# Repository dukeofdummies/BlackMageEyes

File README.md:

# BlackMageEyes
For the code behind the eyes here https://www.youtube.com/watch?v=K9V43iSXRQA

The main gyst of this code is to read button pushes (contact closures) from a controller to change patterns in Adafruit's Neopixel Array.

For details on the Hardware behind it see here
https://www.deviantart.com/dukeofdummies

This current eye pattern is one strand in this orientation zig zagging up and down, many LEDs aren't actually used
```
0   18    36    54 55 56 57 58 59 60   78    96
 1 17 19 35 37 53                  61 77 79 95 97  113
 2 16 20 34 38 52                  62 76 80 94 98  112
 3 15 21 33 39 51                  63 75 81 93 99  111
 4 14 22 32 40 50                  64 74 82 92 100 110
 5 13 23 31 41 49                  65 73 83 91 101 109
 6 12 24 30 42 48                  66 72 84 90 102 108
 7 11 25 29 43 47                  67 71 85 89 103 107
 8 10 26 28 44 46                  68 70 86 88 104 106
  9    27    45                     69    87     105
```

every expression also has a positive number associated with it in the "expression" variable. 
If we're already expressing the expression, the code shouldn't do anything. 
(this saves on quite a bit of power) Each expression is associated with a number.

The general pattern will look like this

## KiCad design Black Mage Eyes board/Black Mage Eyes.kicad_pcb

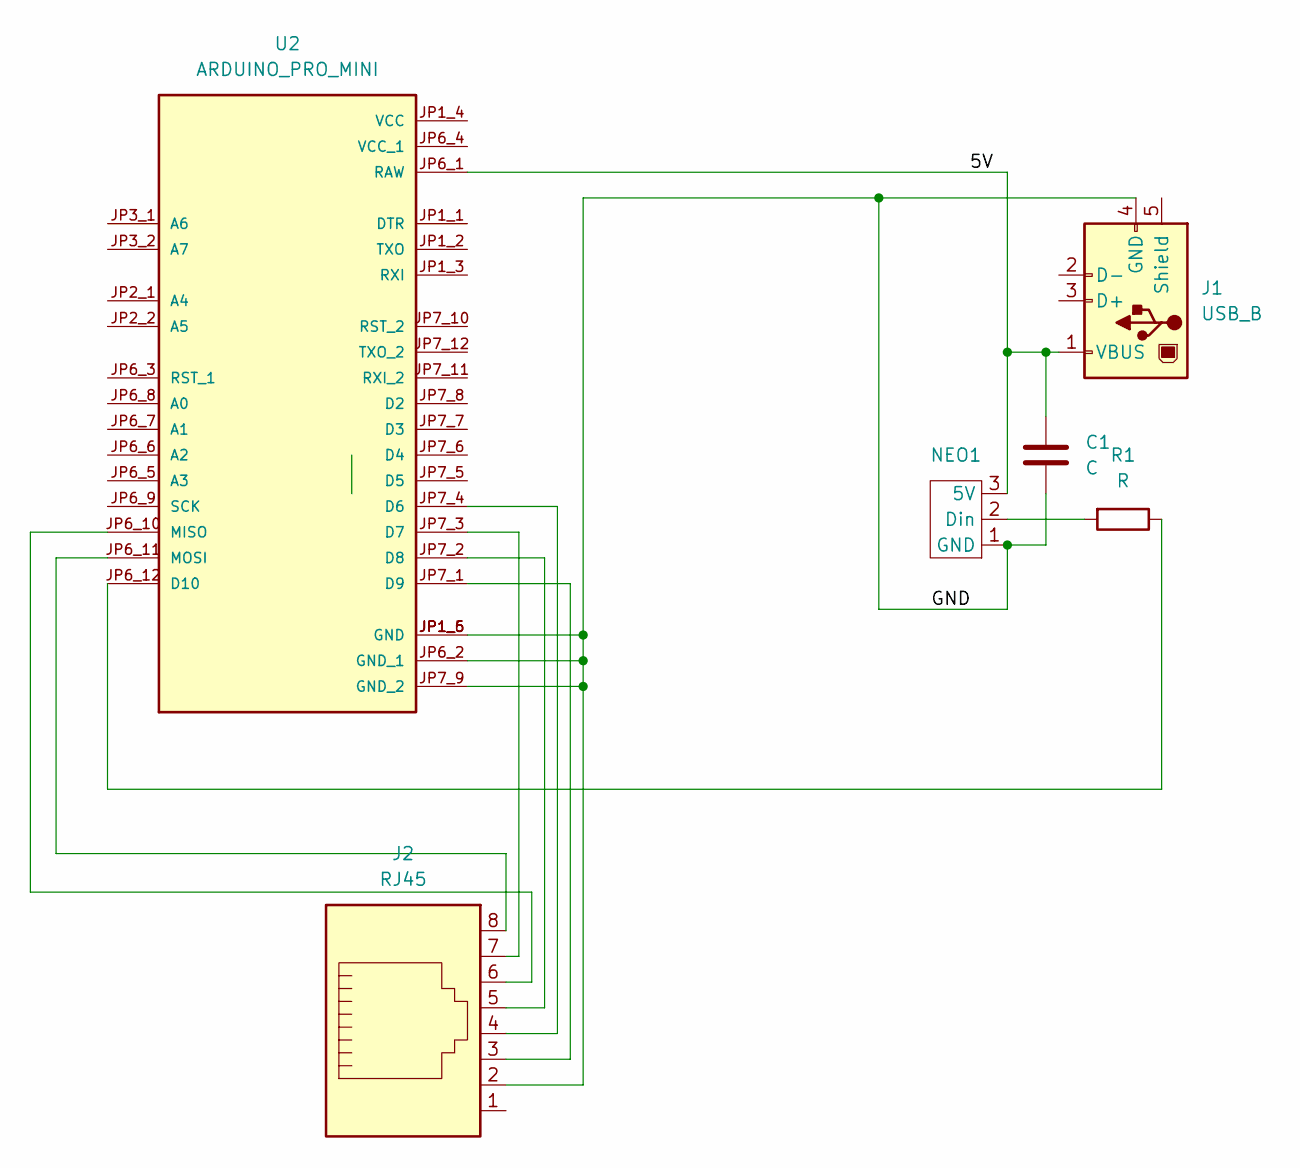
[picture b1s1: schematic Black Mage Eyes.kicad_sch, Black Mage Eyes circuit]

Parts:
C1: C; C_Radial_D8.0mm_H7.0mm_P3.50mm
J1: USB_B; USB_B_Amphenol_MUSB-D511_Vertical_Rugged
J2: RJ45; RJ45_Amphenol_54602-x08_Horizontal
NEO1: PinHeader_1x03_P2.54mm_Vertical
R1: R; R_Axial_DIN0207_L6.3mm_D2.5mm_P7.62mm_Horizontal
U2: ARDUINO_PRO_MINI; MODULE_ARDUINO_PRO_MINI; PARTREV N/A

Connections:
/5V: C1.2, J1.1 (VBUS), NEO1.3 (5V), U2.JP6_1 (RAW)
/GND: C1.1, J1.4 (GND), J2.2, NEO1.1 (GND), U2.JP1_5 (GND), U2.JP1_6 (GND), U2.JP6_2 (GND_1), U2.JP7_9 (GND_2)
unnamed: NEO1.2 (Din), R1.2
unnamed: J2.4, U2.JP7_4 (D6)
unnamed: J2.7, U2.JP7_3 (D7)
unnamed: J2.5, U2.JP7_2 (D8)
unnamed: J2.3, U2.JP7_1 (D9)
unnamed: R1.1, U2.JP6_12 (D10)
unnamed: J2.6, U2.JP6_10 (MISO)
unnamed: J2.8, U2.JP6_11 (MOSI)

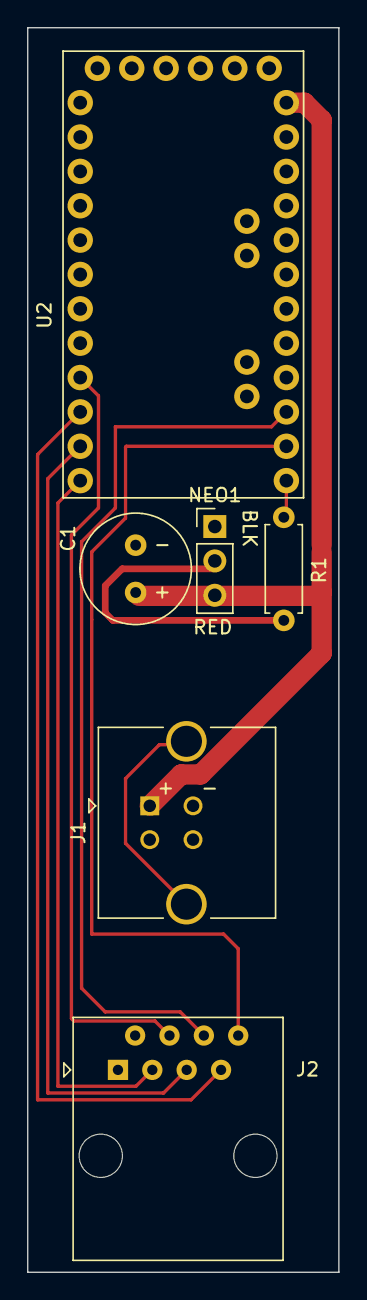
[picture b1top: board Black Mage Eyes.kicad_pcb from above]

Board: 2 copper layers, 23.0 x 92.0 mm, 6 parts (0 on the bottom side), 10 nets.

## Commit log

2019-04-12 The Code behind the eyes
2019-04-12 Uploading Readme
2025-07-31 remade the code to fit smaller memory limited chips, added kikad files for boards compatible with a smaller arduino
2025-07-31 Update README.md
    I drastically need to add more info
2025-07-31 Update README.md
    .md now looks nice
